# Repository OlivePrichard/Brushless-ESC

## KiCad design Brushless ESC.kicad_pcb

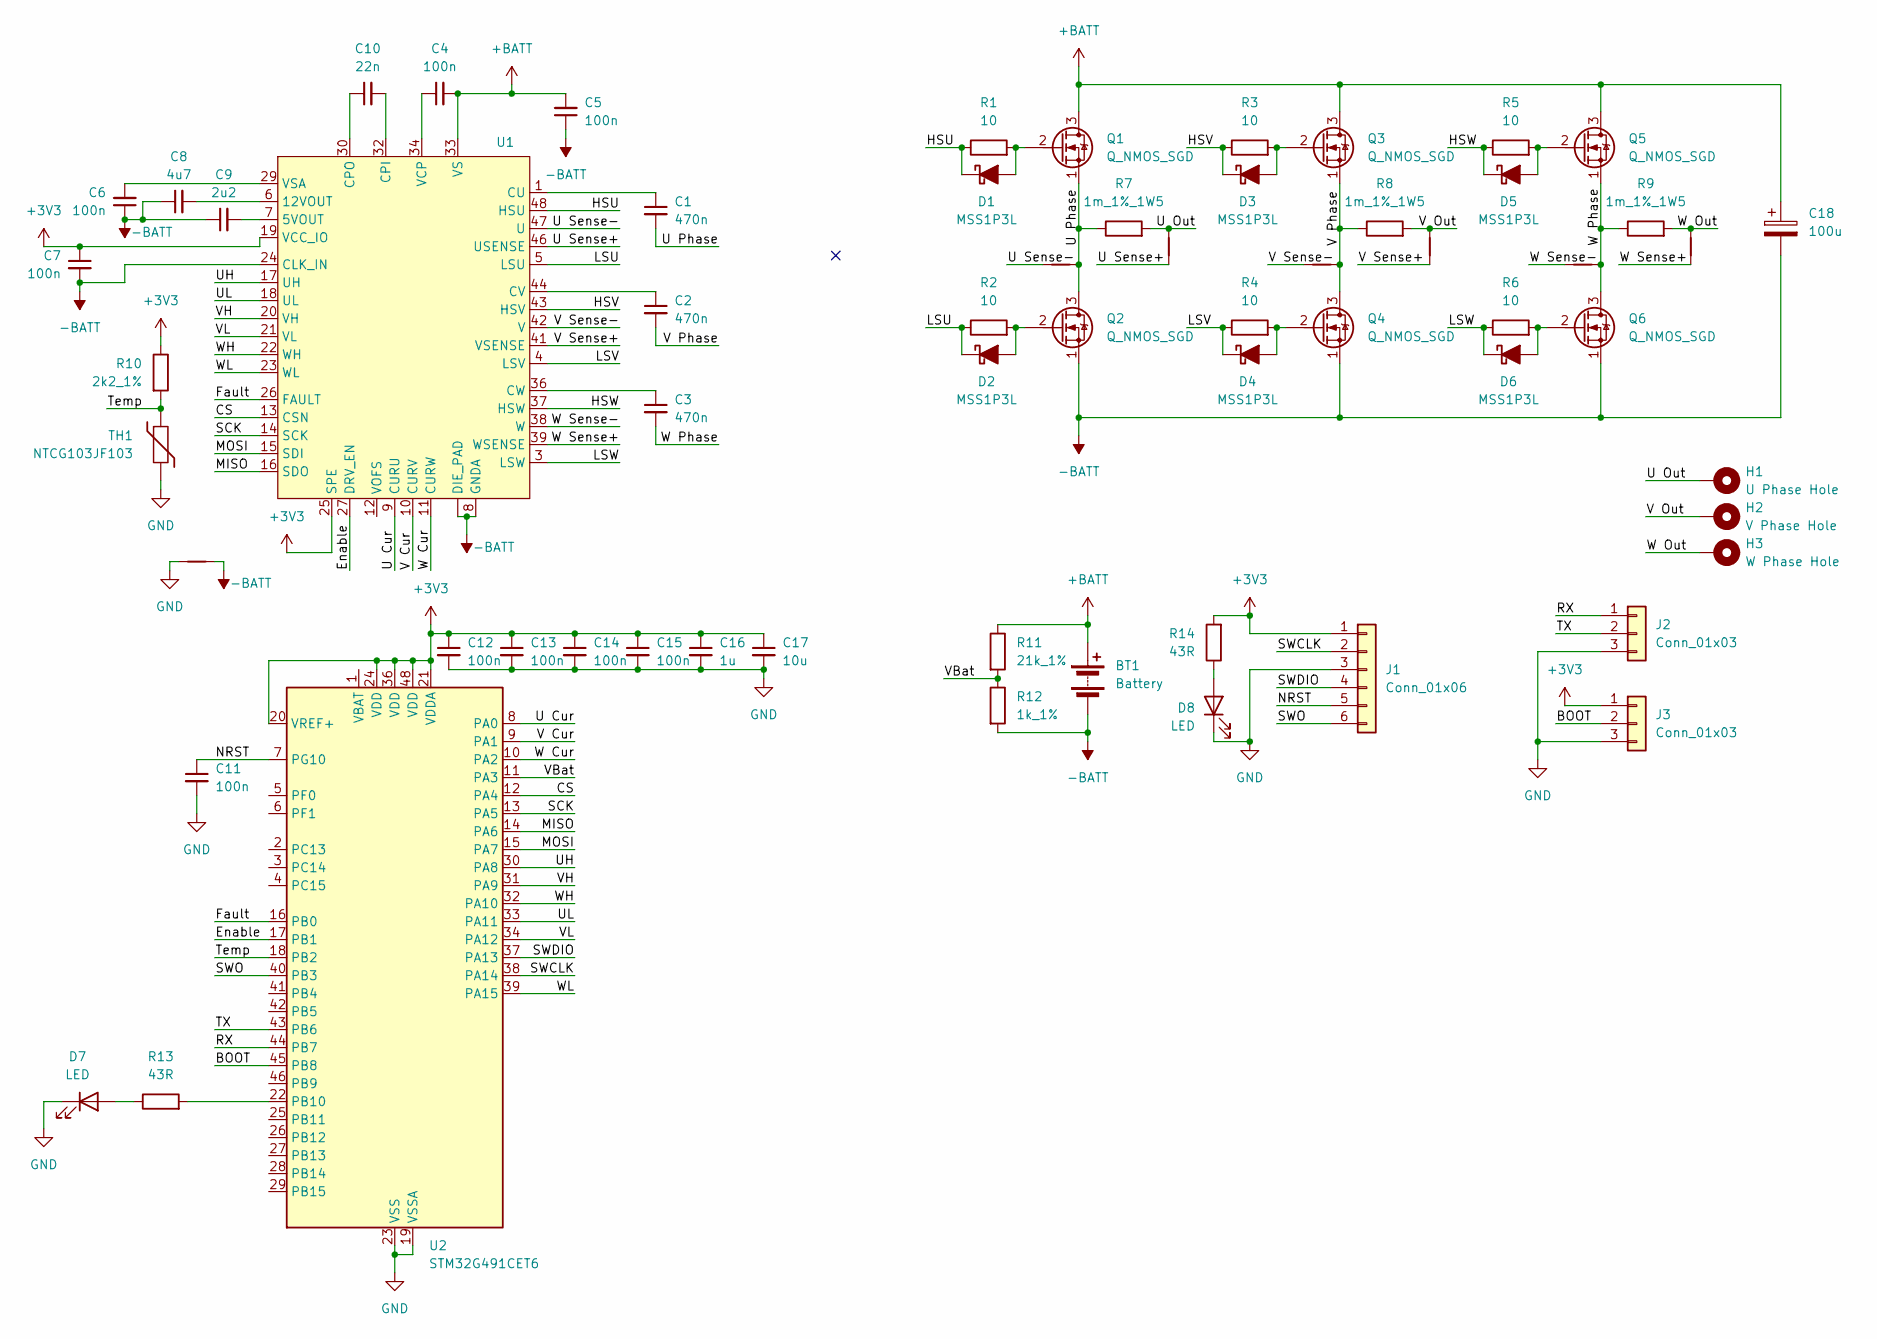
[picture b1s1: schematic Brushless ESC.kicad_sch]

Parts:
BT1: Battery; AMASS_XT30U-F_1x02_P5.0mm_Vertical
C1, C2, C3: 470n; C_0402_1005Metric_Pad0.74x0.62mm_HandSolder
C4, C5, C6: 100n; C_0805_2012Metric_Pad1.18x1.45mm_HandSolder
C7, C11, C12, C13, C14, C15: 100n; C_0402_1005Metric_Pad0.74x0.62mm_HandSolder
C8: 4u7; C_0603_1608Metric_Pad1.08x0.95mm_HandSolder
C9: 2u2; C_0603_1608Metric_Pad1.08x0.95mm_HandSolder
C10: 22n; C_0603_1608Metric_Pad1.08x0.95mm_HandSolder
C16: 1u; C_0402_1005Metric_Pad0.74x0.62mm_HandSolder
C17: 10u; C_0402_1005Metric_Pad0.74x0.62mm_HandSolder
C18: 100u; CP_Elec_10x10
D1, D2, D3, D4, D5, D6: MSS1P3L; D_MicroSMP_AK
D7, D8: LED; D_0603_1608Metric_Pad1.05x0.95mm_HandSolder
H1: U Phase Hole; SolderWire-2.5sqmm_1x01_D2.4mm_OD4.4mm
H2: V Phase Hole; SolderWire-2.5sqmm_1x01_D2.4mm_OD4.4mm
H3: W Phase Hole; SolderWire-2.5sqmm_1x01_D2.4mm_OD4.4mm
J1: Conn_01x06; PinHeader_1x06_P2.54mm_Vertical
J2, J3: Conn_01x03; PinHeader_1x03_P2.54mm_Vertical
NT1, NT2, NT3, NT4, NT5, NT6: NetTie_2; NetTie-2_SMD_Pad0.5mm
NT7: NetTie_2; NetTie-2_THT_Pad0.3mm
Q1, Q2, Q3, Q4, Q5, Q6: Q_NMOS_SGD; 2-5Q1S
R1, R2, R3, R4, R5, R6: 10; R_0402_1005Metric_Pad0.72x0.64mm_HandSolder
R7, R8, R9: 1m_1%_1W5; R_2010_5025Metric_Pad1.40x2.65mm_HandSolder
R10: 2k2_1%; R_0402_1005Metric_Pad0.72x0.64mm_HandSolder
R11: 21k_1%; R_0402_1005Metric_Pad0.72x0.64mm_HandSolder
R12: 1k_1%; R_0402_1005Metric_Pad0.72x0.64mm_HandSolder
R13, R14: 43R; R_0402_1005Metric_Pad0.72x0.64mm_HandSolder
TH1: NTCG103JF103; R_0402_1005Metric_Pad0.72x0.64mm_HandSolder
U1: TQFP-48-1EP_7x7mm_P0.5mm_EP5x5mm
U2: STM32G491CET6; LQFP-48_7x7mm_P0.5mm

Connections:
+3V3: C7.1, C12.1, C13.1, C14.1, C15.1, C16.1, C17.1, J1.1, J3.1, R10.1, R14.2, U1.19 (VCC_IO), U1.25 (SPE), U2.20 (VREF+), U2.21 (VDDA), U2.24 (VDD), U2.36 (VDD), U2.48 (VDD)
+BATT: BT1.1 (+), C4.2, C5.2, C18.1, Q1.3 (D), Q3.3 (D), Q5.3 (D), R11.1, U1.33 (VS)
-BATT: BT1.2 (-), C5.1, C6.1, C7.2, C8.1, C9.1, C18.2, NT7.2, Q2.1 (S), Q4.1 (S), Q6.1 (S), R12.2, U1. (DIE_PAD), U1.8 (GNDA), U1.24 (CLK_IN)
/BOOT: J3.2, U2.45 (PB8)
/CS: U1.13 (CSN), U2.12 (PA4)
/Enable: U1.27 (DRV_EN), U2.17 (PB1)
/Fault: U1.26 (FAULT), U2.16 (PB0)
/HSU: D1.1 (K), R1.1, U1.48 (HSU)
/HSV: D3.1 (K), R3.1, U1.43 (HSV)
/HSW: D5.1 (K), R5.1, U1.37 (HSW)
/LSU: D2.1 (K), R2.1, U1.5 (LSU)
/LSV: D4.1 (K), R4.1, U1.4 (LSV)
/LSW: D6.1 (K), R6.1, U1.3 (LSW)
/MISO: U1.16 (SDO), U2.14 (PA6)
/MOSI: U1.15 (SDI), U2.15 (PA7)
/NRST: C11.1, J1.5, U2.7 (PG10)
/RX: J2.1, U2.44 (PB7)
/SCK: U1.14 (SCK), U2.13 (PA5)
/SWCLK: J1.2, U2.38 (PA14)
/SWDIO: J1.4, U2.37 (PA13)
/SWO: J1.6, U2.40 (PB3)
/TX: J2.2, U2.43 (PB6)
/Temp: R10.2, TH1.1, U2.18 (PB2)
/U Cur: U1.9 (CURU), U2.8 (PA0)
/U Out: H1.1, NT2.2, R7.2
/U Phase: C1.2, NT1.1, Q1.1 (S), Q2.3 (D), R7.1
/U Sense+: NT2.1, U1.46 (USENSE)
/U Sense-: NT1.2, U1.47 (U)
/UH: U1.17 (UH), U2.30 (PA8)
/UL: U1.18 (UL), U2.33 (PA11)
/V Cur: U1.10 (CURV), U2.9 (PA1)
/V Out: H2.1, NT4.2, R8.2
/V Phase: C2.2, NT3.1, Q3.1 (S), Q4.3 (D), R8.1
/V Sense+: NT4.1, U1.41 (VSENSE)
/V Sense-: NT3.2, U1.42 (V)
/VBat: R11.2, R12.1, U2.11 (PA3)
/VH: U1.20 (VH), U2.31 (PA9)
/VL: U1.21 (VL), U2.34 (PA12)
/W Cur: U1.11 (CURW), U2.10 (PA2)
/W Out: H3.1, NT6.2, R9.2
/W Phase: C3.2, NT5.1, Q5.1 (S), Q6.3 (D), R9.1
/W Sense+: NT6.1, U1.39 (WSENSE)
/W Sense-: NT5.2, U1.38 (W)
/WH: U1.22 (WH), U2.32 (PA10)
/WL: U1.23 (WL), U2.39 (PA15)
GND: C11.2, C12.2, C13.2, C14.2, C15.2, C16.2, C17.2, D7.1 (K), D8.1 (K), J1.3, J2.3, J3.3, NT7.1, TH1.2, U2.19 (VSSA), U2.23 (VSS), U2.35 (VSS), U2.47 (VSS)
unnamed: D1.2 (A), Q1.2 (G), R1.2
unnamed: D2.2 (A), Q2.2 (G), R2.2
unnamed: D3.2 (A), Q3.2 (G), R3.2
unnamed: D4.2 (A), Q4.2 (G), R4.2
unnamed: D5.2 (A), Q5.2 (G), R5.2
unnamed: D6.2 (A), Q6.2 (G), R6.2
unnamed: D7.2 (A), R13.1
unnamed: D8.2 (A), R14.1
unnamed: C9.2, U1.7 (5VOUT)
unnamed: C8.2, U1.6 (12VOUT)
unnamed: C10.2, U1.32 (CPI)
unnamed: C10.1, U1.30 (CPO)
unnamed: C1.1, U1.1 (CU)
unnamed: C2.1, U1.44 (CV)
unnamed: C3.1, U1.36 (CW)
unnamed: C4.1, U1.34 (VCP)
unnamed: C6.2, U1.29 (VSA)
unnamed: R13.2, U2.22 (PB10)

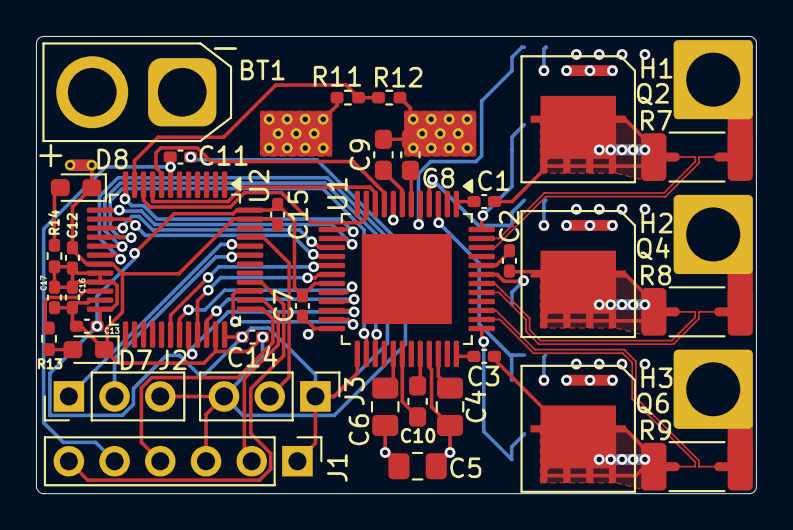
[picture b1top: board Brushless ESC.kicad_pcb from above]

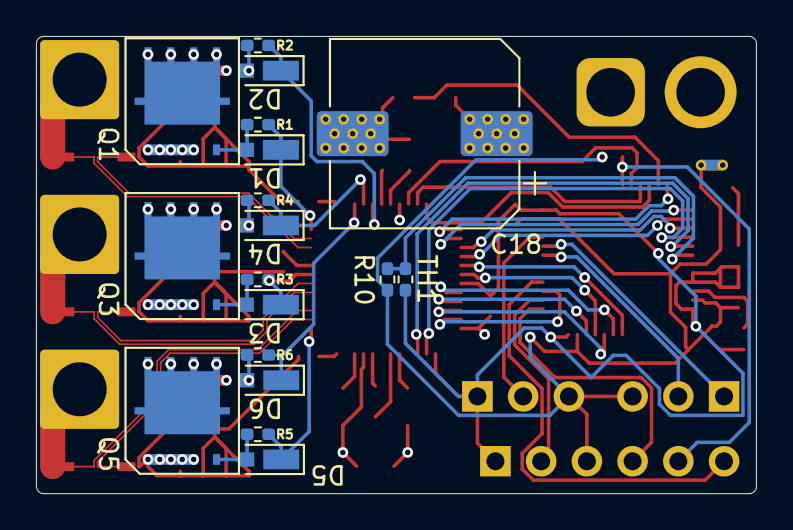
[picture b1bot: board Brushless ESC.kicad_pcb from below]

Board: 4 copper layers, 40.0 x 25.4 mm, 63 parts (18 on the bottom side), 64 nets.

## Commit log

2025-05-16 i should probably back this up or something idk
2025-08-18 syncing
2025-08-21 created project
2025-08-21 closed kicad
